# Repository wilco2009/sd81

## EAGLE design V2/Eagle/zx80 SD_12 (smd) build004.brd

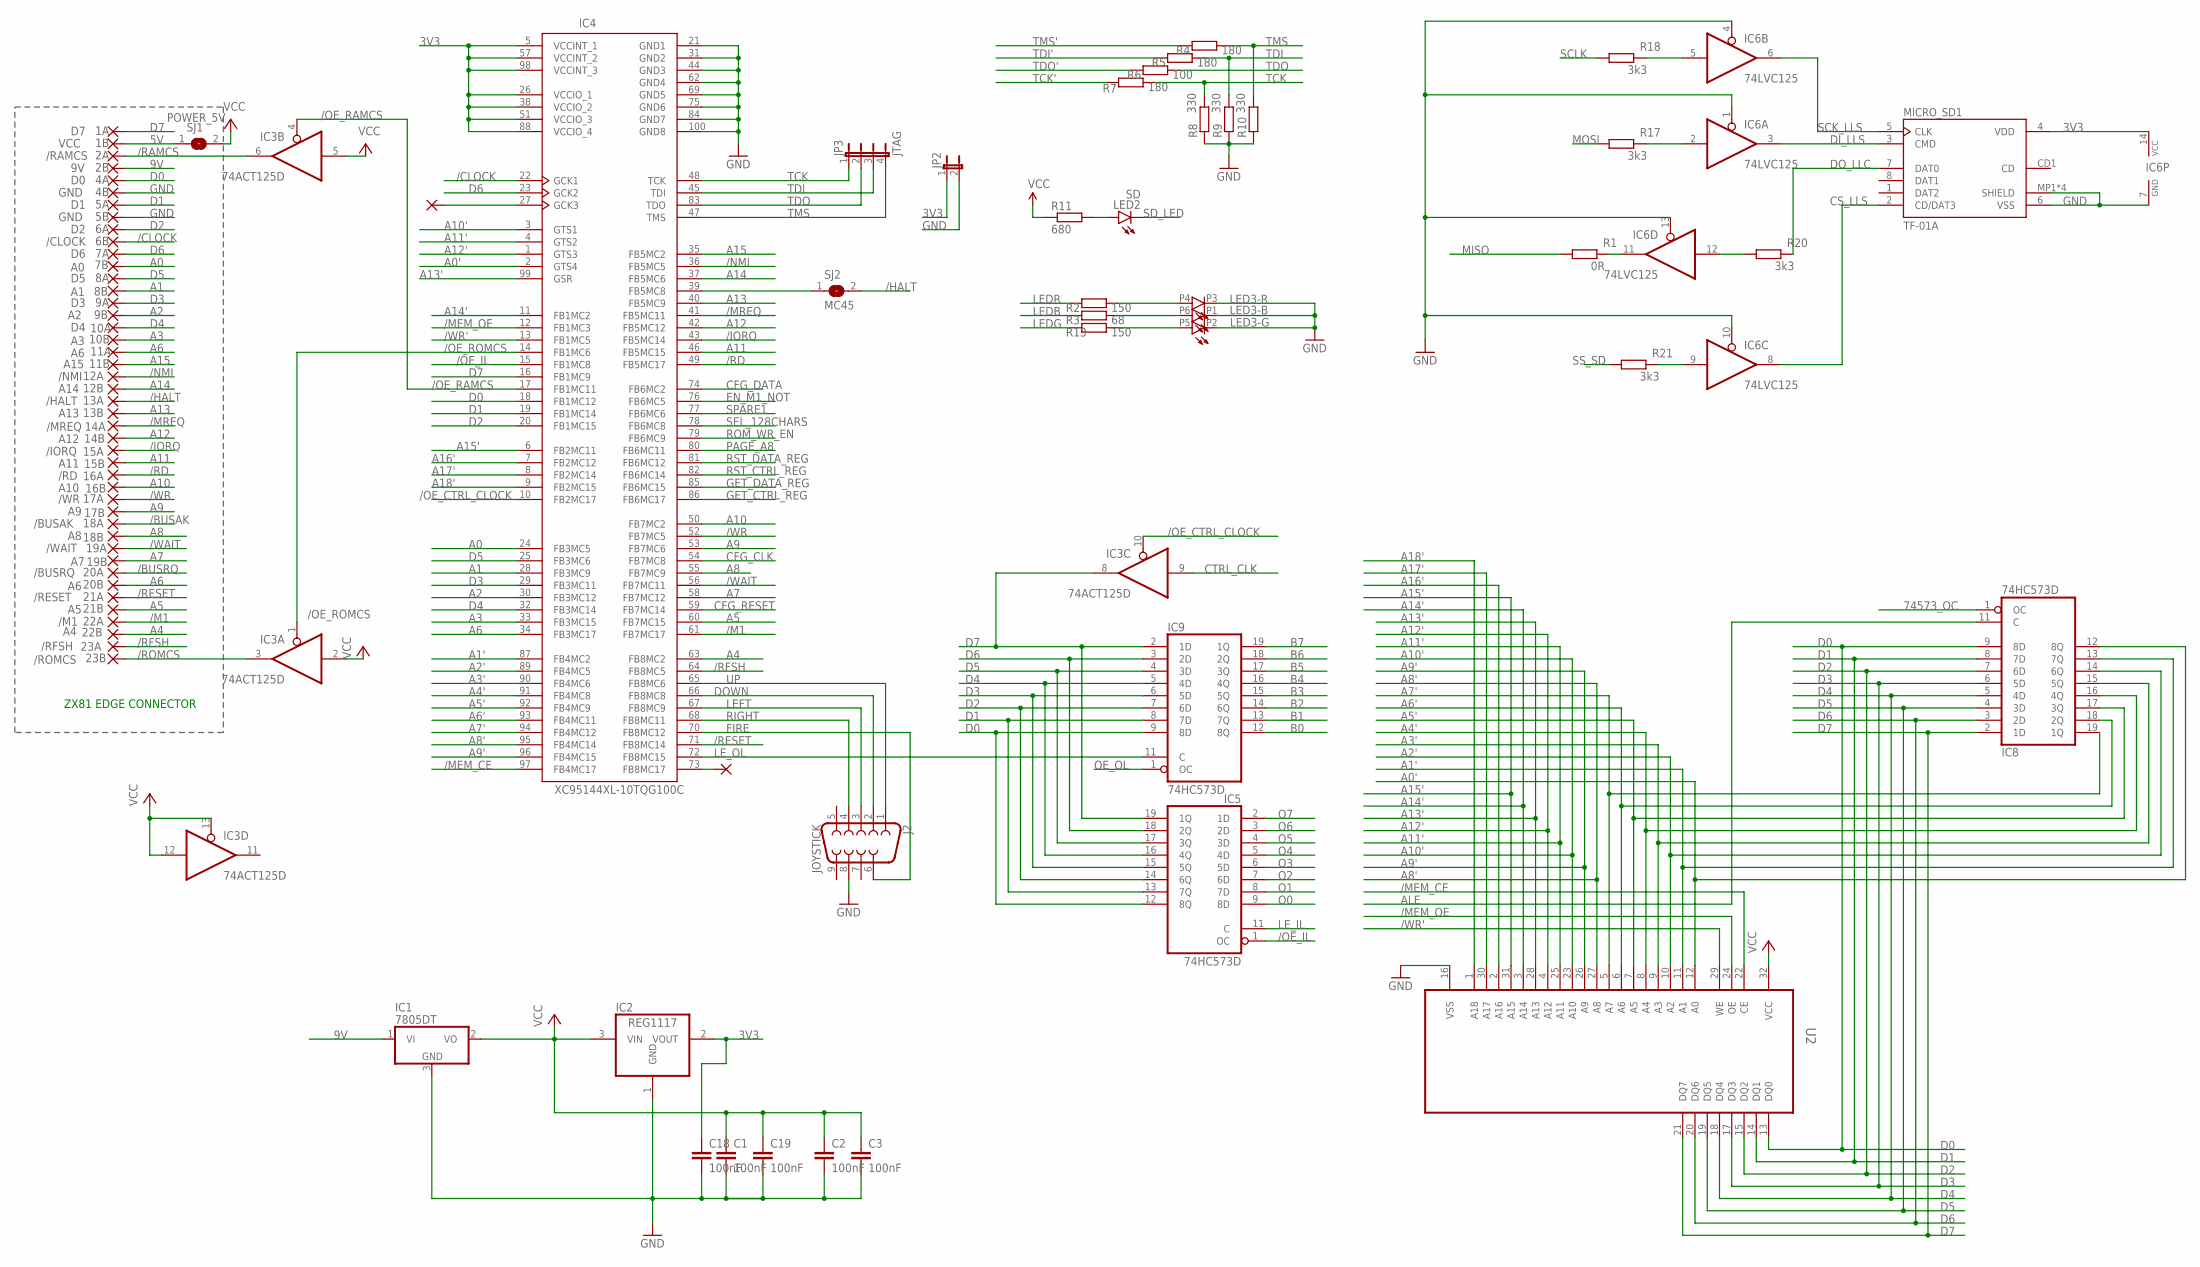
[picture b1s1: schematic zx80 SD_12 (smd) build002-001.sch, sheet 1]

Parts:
1A: D7; EDGEPIN
1B: VCC; EDGEPIN
2A: /RAMCS; EDGEPIN
2B: 9V; EDGEPIN
4A: D0; EDGEPIN
4B, 5B: GND; EDGEPIN
5A: D1; EDGEPIN
6A: D2; EDGEPIN
6B: /CLOCK; EDGEPIN
7A: D6; EDGEPIN
7B: A0; EDGEPIN
8A: D5; EDGEPIN
8B: A1; EDGEPIN
9A: D3; EDGEPIN
9B: A2; EDGEPIN
10A: D4; EDGEPIN
10B: A3; EDGEPIN
11A, 20B: A6; EDGEPIN
11B: A15; EDGEPIN
12A: /NMI; EDGEPIN
12B: A14; EDGEPIN
13A: /HALT; EDGEPIN
13B: A13; EDGEPIN
14A: /MREQ; EDGEPIN
14B: A12; EDGEPIN
15A: /IORQ; EDGEPIN
15B: A11; EDGEPIN
16A: /RD; EDGEPIN
16B: A10; EDGEPIN
17A: /WR; EDGEPIN
17B: A9; EDGEPIN
18A: /BUSAK; EDGEPIN
18B: A8; EDGEPIN
19A: /WAIT; EDGEPIN
19B: A7; EDGEPIN
20A: /BUSRQ; EDGEPIN
21A: /RESET; EDGEPIN
21B: A5; EDGEPIN
22A: /M1; EDGEPIN
22B: A4; EDGEPIN
23A: /RFSH; EDGEPIN
23B: /ROMCS; EDGEPIN
C1, C2, C3, C18, C19: 100nF; C0603
IC1: 7805DT; TO252
IC2: REG1117; SOT223
IC3: 74ACT125D; SO14
IC4: XC95144XL-10TQG100C; TQFP100
IC5, IC8, IC9: 74HC573D; SO20W
IC6: 74LVC125; SO14
J2: JOYSTICK; DB9_MALE
JP2: JP1E; JP1
JP3: JTAG; JP4
LED2: SD; CHIPLED_0603
LED3: RS-3535MWAR; 3535-PLCC6
MICRO_SD1: TF-01A
PAD1: 1,6/0,8
PAD6: P73; 1,6/0,8
R1: 0R; R0603
R2, R13: 150; R0603
R3: 68; R0603
R4, R5, R7: 180; R0603
R6: 100; R0603
R8, R9, R10: 330; R0603
R11: 680; R0603
R17, R18, R20, R21: 3k3; R0603
SJ1: POWER_5V; SJ
SJ2: MC45; SJ
U2: AS6C4008-55SINSOP5; SOP32-5

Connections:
3V3: C18.1, IC2.2 (VOUT), IC4.5 (VCCINT_1), IC4.26 (VCCIO_1), IC4.38 (VCCIO_2), IC4.51 (VCCIO_3), IC4.57 (VCCINT_2), IC4.88 (VCCIO_4), IC4.98 (VCCINT_3), IC6.14 (VCC), JP2.1, MICRO_SD1.4 (VDD); also elsewhere on the board
5V: 1B.1, SJ1.1
9V: 2B.1, IC1.1 (VI)
/BUSAK: 18A.1
/BUSRQ: 20A.1
/CLOCK: 6B.1, IC4.22 (GCK1); also elsewhere on the board
/HALT: 13A.1, SJ2.2
/IORQ: 15A.1, IC4.43 (FB5MC14); also elsewhere on the board
/M1: 22A.1, IC4.61 (FB7MC17); also elsewhere on the board
/MEM_CE: IC4.97 (FB4MC17), U2.22 (CE); also elsewhere on the board
/MEM_OE: IC4.12 (FB1MC3), U2.24 (OE); also elsewhere on the board
/MREQ: 14A.1, IC4.41 (FB5MC11); also elsewhere on the board
/NMI: 12A.1, IC4.36 (FB5MC5); also elsewhere on the board
/OE_CTRL_CLOCK: IC3.10 (OE), IC4.10 (FB2MC17)
/OE_RAMCS: IC3.4 (OE), IC4.17 (FB1MC11)
/OE_ROMCS: IC3.1 (OE), IC4.14 (FB1MC6)
/RAMCS: 2A.1, IC3.6 (O); also elsewhere on the board
/RD: 16A.1, IC4.49 (FB5MC17); also elsewhere on the board
/RESET: 21A.1, IC4.71 (FB8MC14); also elsewhere on the board
/RFSH: 23A.1, IC4.64 (FB8MC5); also elsewhere on the board
/ROMCS: 23B.1, IC3.3 (O); also elsewhere on the board
/WAIT: 19A.1, IC4.56 (FB7MC11); also elsewhere on the board
/WR: 17A.1, IC4.52 (FB7MC5); also elsewhere on the board
/WR': IC4.13 (FB1MC5), U2.29 (WE); also elsewhere on the board
A0: 7B.1, IC4.24 (FB3MC5); also elsewhere on the board
A0': IC4.2 (GTS4), IC8.12 (8Q), U2.12 (A0); also elsewhere on the board
A1: 8B.1, IC4.28 (FB3MC9); also elsewhere on the board
A1': IC4.87 (FB4MC2), IC8.13 (7Q), U2.11 (A1); also elsewhere on the board
A2: 9B.1, IC4.30 (FB3MC12); also elsewhere on the board
A2': IC4.89 (FB4MC5), IC8.14 (6Q), U2.10 (A2); also elsewhere on the board
A3: 10B.1, IC4.33 (FB3MC15); also elsewhere on the board
A3': IC4.90 (FB4MC6), IC8.15 (5Q), U2.9 (A3); also elsewhere on the board
A4: 22B.1, IC4.63 (FB8MC2); also elsewhere on the board
A4': IC4.91 (FB4MC8), IC8.16 (4Q), U2.8 (A4); also elsewhere on the board
A5: 21B.1, IC4.60 (FB7MC15); also elsewhere on the board
A5': IC4.92 (FB4MC9), IC8.17 (3Q), U2.7 (A5); also elsewhere on the board
A6: 11A.1, 20B.1, IC4.34 (FB3MC17); also elsewhere on the board
A6': IC4.93 (FB4MC11), IC8.18 (2Q), U2.6 (A6); also elsewhere on the board
A7: 19B.1, IC4.58 (FB7MC12); also elsewhere on the board
A7': IC4.94 (FB4MC12), IC8.19 (1Q), U2.5 (A7); also elsewhere on the board
A8: 18B.1, IC4.55 (FB7MC9); also elsewhere on the board
A8': IC4.95 (FB4MC14), U2.27 (A8); also elsewhere on the board
A9: 17B.1, IC4.53 (FB7MC6); also elsewhere on the board
A9': IC4.96 (FB4MC15), U2.26 (A9); also elsewhere on the board
A10: 16B.1, IC4.50 (FB7MC2); also elsewhere on the board
A10': IC4.3 (GTS1), U2.23 (A10); also elsewhere on the board
A11: 15B.1, IC4.46 (FB5MC15); also elsewhere on the board
A11': IC4.4 (GTS2), U2.25 (A11); also elsewhere on the board
A12: 14B.1, IC4.42 (FB5MC12); also elsewhere on the board
A12': IC4.1 (GTS3), U2.4 (A12); also elsewhere on the board
A13: 13B.1, IC4.40 (FB5MC9); also elsewhere on the board
A13': IC4.99 (GSR), U2.28 (A13); also elsewhere on the board
A14: 12B.1, IC4.37 (FB5MC6); also elsewhere on the board
A14': IC4.11 (FB1MC2), U2.3 (A14); also elsewhere on the board
A15: 11B.1, IC4.35 (FB5MC2); also elsewhere on the board
A15': IC4.6 (FB2MC11), U2.31 (A15); also elsewhere on the board
A16': IC4.7 (FB2MC12), U2.2 (A16); also elsewhere on the board
A17': IC4.8 (FB2MC14), U2.30 (A17); also elsewhere on the board
A18': IC4.9 (FB2MC15), U2.1 (A18); also elsewhere on the board
ALE: IC8.11 (C); also elsewhere on the board
B0: IC9.12 (8Q); also elsewhere on the board
B1: IC9.13 (7Q); also elsewhere on the board
B2: IC9.14 (6Q); also elsewhere on the board
B3: IC9.15 (5Q); also elsewhere on the board
B4: IC9.16 (4Q); also elsewhere on the board
B5: IC9.17 (3Q); also elsewhere on the board
B6: IC9.18 (2Q); also elsewhere on the board
B7: IC9.19 (1Q); also elsewhere on the board
CFG_CLK: IC4.54 (FB7MC8); also elsewhere on the board
CFG_DATA: IC4.74 (FB6MC2); also elsewhere on the board
CFG_RESET: IC4.59 (FB7MC14); also elsewhere on the board
CS_LLS: IC6.8 (O), MICRO_SD1.2 (CD/DAT3)
CTRL_CLK: IC3.9 (I); also elsewhere on the board
D0: 4A.1, IC4.18 (FB1MC12), IC5.12 (8Q), IC8.9 (8D), IC9.9 (8D), U2.13 (DQ0); also elsewhere on the board
D1: 5A.1, IC4.19 (FB1MC14), IC5.13 (7Q), IC8.8 (7D), IC9.8 (7D), U2.14 (DQ1); also elsewhere on the board
D2: 6A.1, IC4.20 (FB1MC15), IC5.14 (6Q), IC8.7 (6D), IC9.7 (6D), U2.15 (DQ2); also elsewhere on the board
D3: 9A.1, IC4.29 (FB3MC11), IC5.15 (5Q), IC8.6 (5D), IC9.6 (5D), U2.17 (DQ3); also elsewhere on the board
D4: 10A.1, IC4.32 (FB3MC14), IC5.16 (4Q), IC8.5 (4D), IC9.5 (4D), U2.18 (DQ4); also elsewhere on the board
D5: 8A.1, IC4.25 (FB3MC6), IC5.17 (3Q), IC8.4 (3D), IC9.4 (3D), U2.19 (DQ5); also elsewhere on the board
D6: 7A.1, IC4.23 (GCK2), IC5.18 (2Q), IC8.3 (2D), IC9.3 (2D), U2.20 (DQ6); also elsewhere on the board
D7: 1A.1, IC3.8 (O), IC4.16 (FB1MC9), IC5.19 (1Q), IC8.2 (1D), IC9.2 (1D), U2.21 (DQ7); also elsewhere on the board
DI_LLS: IC6.3 (O), MICRO_SD1.3 (CMD)
DOWN: IC4.66 (FB8MC8), J2.2; also elsewhere on the board
DO_LLC: IC6.12 (I), R20.1
EN_M1_NOT: IC4.76 (FB6MC5); also elsewhere on the board
FIRE: IC4.70 (FB8MC12), J2.6; also elsewhere on the board
GET_CTRL_REG: IC4.86 (FB6MC17); also elsewhere on the board
GET_DATA_REG: IC4.85 (FB6MC15); also elsewhere on the board
LEDB: R3.1; also elsewhere on the board
LEDG: R13.1; also elsewhere on the board
LEDR: R2.1; also elsewhere on the board
LEFT: IC4.67 (FB8MC9), J2.3; also elsewhere on the board
LE_IL: IC5.11 (C); also elsewhere on the board
LE_OL: IC4.72 (FB8MC15), IC9.11 (C)
MISO: R1.1; also elsewhere on the board
MOSI: R17.1; also elsewhere on the board
unnamed: IC6.2 (I), R17.2
unnamed: IC6.11 (O), R1.2
unnamed: IC6.5 (I), R18.2
unnamed: MICRO_SD1.7 (DAT0), R20.2
unnamed: IC6.9 (I), R21.2
unnamed: LED2.A, R11.2
unnamed: IC4.73 (FB8MC17), PAD6.1
unnamed: IC4.27 (GCK3), PAD1.1
unnamed: LED3.P4 (A), R2.2
unnamed: LED3.P6 (A), R3.2
unnamed: LED3.P5 (A), R13.2
O0: IC5.9 (8D); also elsewhere on the board
O1: IC5.8 (7D); also elsewhere on the board
O2: IC5.7 (6D); also elsewhere on the board
O3: IC5.6 (5D); also elsewhere on the board
O4: IC5.5 (4D); also elsewhere on the board
O5: IC5.4 (3D); also elsewhere on the board
PAGE_A8: IC4.80 (FB6MC11); also elsewhere on the board
RIGHT: IC4.68 (FB8MC11), J2.4; also elsewhere on the board
ROM_WR_EN: IC4.79 (FB6MC9); also elsewhere on the board
RST_CTRL_REG: IC4.82 (FB6MC14); also elsewhere on the board
RST_DATA_REG: IC4.81 (FB6MC12); also elsewhere on the board
SCK_LLS: IC6.6 (O), MICRO_SD1.5 (CLK)
SCLK: R18.1; also elsewhere on the board
SD_LED: LED2.C; also elsewhere on the board
SEL_128CHARS: IC4.78 (FB6MC8); also elsewhere on the board
SPARE1: IC4.77 (FB6MC6); also elsewhere on the board
SS_SD: R21.1; also elsewhere on the board
TCK: IC4.48 (TCK), JP3.1, R7.2, R8.2; also elsewhere on the board
TCK': R7.1; also elsewhere on the board
TDI: IC4.45 (TDI), JP3.3, R5.2, R9.2; also elsewhere on the board
TDI': R5.1; also elsewhere on the board
TDO: IC4.83 (TDO), JP3.2, R6.2; also elsewhere on the board
TDO': R6.1; also elsewhere on the board
TMS: IC4.47 (TMS), JP3.4, R4.2, R10.2; also elsewhere on the board
TMS': R4.1; also elsewhere on the board
UP: IC4.65 (FB8MC6), J2.1; also elsewhere on the board

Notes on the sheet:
ZX81 EDGE CONNECTOR

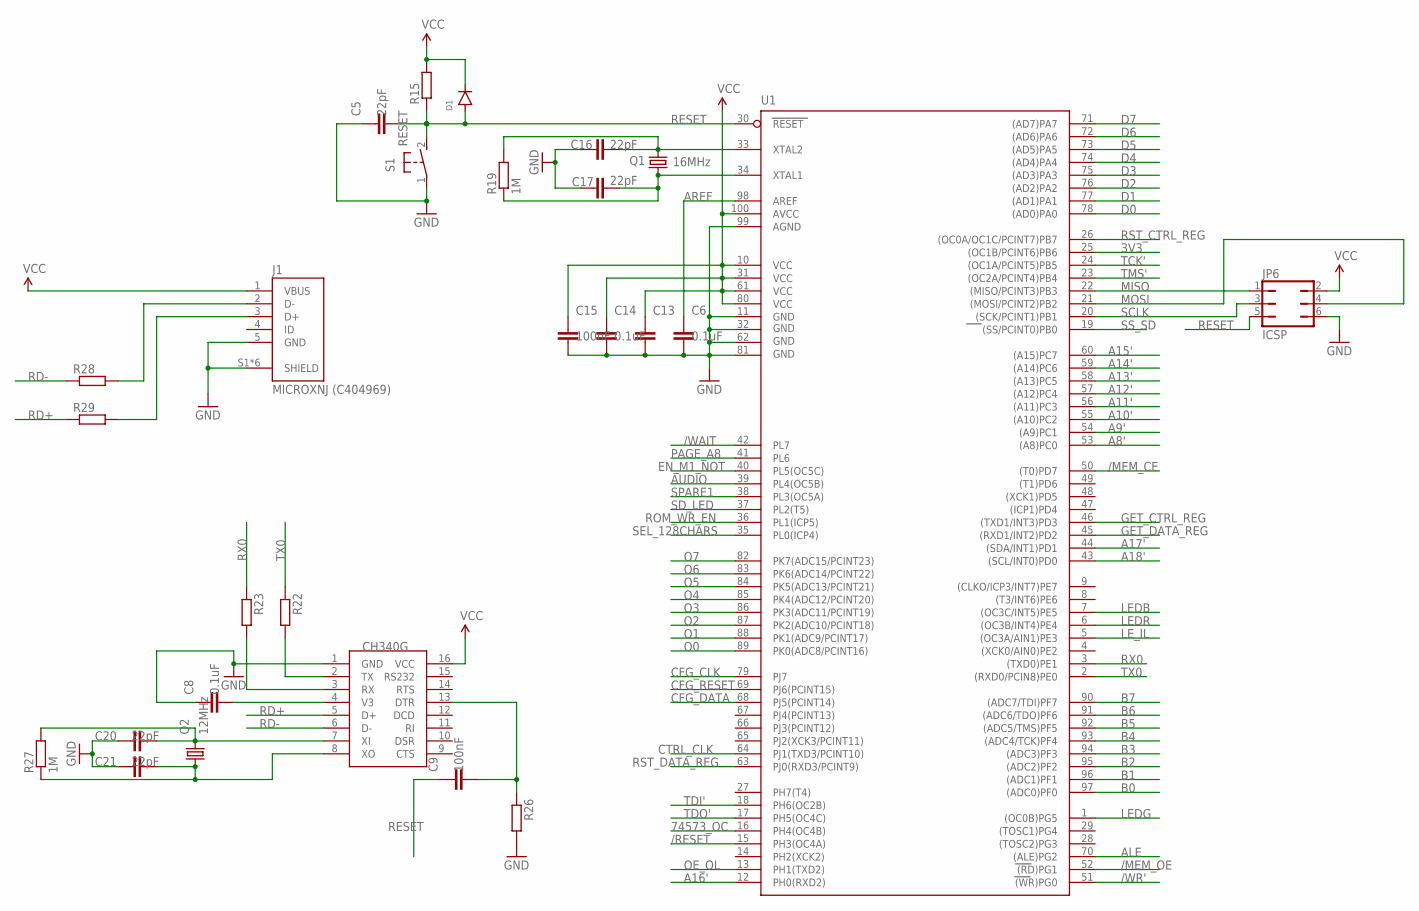
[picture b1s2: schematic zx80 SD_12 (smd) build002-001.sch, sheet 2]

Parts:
C5, C16, C17, C20, C21: 22pF; C0603
C6, C8, C13, C14: 0.1uF; C0603
C9, C15: 100nF; C0603
D1: DIODE-SOD123; SOD123
IC7: CH340G; SOIC16
J1: MICROXNJ (C404969); SHOUHAN_MICROXNJ
JP6: ICSP; JP3Q
Q1: 16MHz; 3.2X2.5_KX-7
Q2: 12MHz; 3.2X2.5_KX-7
R15: R0603
R19, R27: 1M; R0603
R22, R23, R26: 1K; R0603
R28, R29: 22R; R0603
S1: RESET; B3F-31XX
U1: ATMEGA2560AU; TQFP100

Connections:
3V3: U1.25 ((OC1B/PCINT6)PB6); also elsewhere on the board
/MEM_CE: U1.50 ((T0)PD7); also elsewhere on the board
/MEM_OE: U1.52 ((RD)PG1); also elsewhere on the board
/RESET: U1.15 (PH3(OC4A)); also elsewhere on the board
/WAIT: U1.42 (PL7); also elsewhere on the board
/WR': U1.51 ((WR)PG0); also elsewhere on the board
A8': U1.53 ((A8)PC0); also elsewhere on the board
A9': U1.54 ((A9)PC1); also elsewhere on the board
A10': U1.55 ((A10)PC2); also elsewhere on the board
A11': U1.56 ((A11)PC3); also elsewhere on the board
A12': U1.57 ((A12)PC4); also elsewhere on the board
A13': U1.58 ((A13)PC5); also elsewhere on the board
A14': U1.59 ((A14)PC6); also elsewhere on the board
A15': U1.60 ((A15)PC7); also elsewhere on the board
A16': U1.12 (PH0(RXD2)); also elsewhere on the board
ALE: U1.70 ((ALE)PG2); also elsewhere on the board
AREF: C6.1, U1.98 (AREF)
AUDIO: U1.39 (PL4(OC5B))
B0: U1.97 ((ADC0)PF0); also elsewhere on the board
B1: U1.96 ((ADC1)PF1); also elsewhere on the board
B2: U1.95 ((ADC2)PF2); also elsewhere on the board
B3: U1.94 ((ADC3)PF3); also elsewhere on the board
B4: U1.93 ((ADC4/TCK)PF4); also elsewhere on the board
B5: U1.92 ((ADC5/TMS)PF5); also elsewhere on the board
B6: U1.91 ((ADC6/TDO)PF6); also elsewhere on the board
B7: U1.90 ((ADC7/TDI)PF7); also elsewhere on the board
CFG_CLK: U1.79 (PJ7); also elsewhere on the board
CFG_DATA: U1.68 (PJ5(PCINT14)); also elsewhere on the board
CFG_RESET: U1.69 (PJ6(PCINT15)); also elsewhere on the board
CTRL_CLK: U1.64 (PJ1(TXD3/PCINT10)); also elsewhere on the board
D0: U1.78 ((AD0)PA0); also elsewhere on the board
D1: U1.77 ((AD1)PA1); also elsewhere on the board
D2: U1.76 ((AD2)PA2); also elsewhere on the board
D3: U1.75 ((AD3)PA3); also elsewhere on the board
D4: U1.74 ((AD4)PA4); also elsewhere on the board
D5: U1.73 ((AD5)PA5); also elsewhere on the board
D6: U1.72 ((AD6)PA6); also elsewhere on the board
D7: U1.71 ((AD7)PA7); also elsewhere on the board
EN_M1_NOT: U1.40 (PL5(OC5C)); also elsewhere on the board
GET_CTRL_REG: U1.46 ((TXD1/INT3)PD3); also elsewhere on the board
GET_DATA_REG: U1.45 ((RXD1/INT2)PD2); also elsewhere on the board
LEDB: U1.7 ((OC3C/INT5)PE5); also elsewhere on the board
LEDG: U1.1 ((OC0B)PG5); also elsewhere on the board
LEDR: U1.6 ((OC3B/INT4)PE4); also elsewhere on the board
LE_IL: U1.5 ((OC3A/AIN1)PE3); also elsewhere on the board
MISO: JP6.1, U1.22 ((MISO/PCINT3)PB3); also elsewhere on the board
MOSI: JP6.4, U1.21 ((MOSI/PCINT2)PB2); also elsewhere on the board
unnamed: IC7.2 (TX), R22.2
unnamed: IC7.3 (RX), R23.2
unnamed: C8.2, IC7.4 (V3)
unnamed: C20.2, IC7.7 (XI), Q2.3 (2), R27.2
unnamed: C21.2, IC7.8 (XO), Q2.1, R27.1
unnamed: C16.2, Q1.3 (2), R19.2, U1.33 (XTAL2)
unnamed: C17.2, Q1.1, R19.1, U1.34 (XTAL1)
unnamed: C9.2, IC7.13 (DTR), R26.1
unnamed: J1.2 (D-), R28.2
unnamed: J1.3 (D+), R29.2
O0: U1.89 (PK0(ADC8/PCINT16)); also elsewhere on the board
O1: U1.88 (PK1(ADC9/PCINT17)); also elsewhere on the board
O2: U1.87 (PK2(ADC10/PCINT18)); also elsewhere on the board
O3: U1.86 (PK3(ADC11/PCINT19)); also elsewhere on the board
O4: U1.85 (PK4(ADC12/PCINT20)); also elsewhere on the board
O5: U1.84 (PK5(ADC13/PCINT21)); also elsewhere on the board
PAGE_A8: U1.41 (PL6); also elsewhere on the board
RD+: IC7.5 (D+), R29.1
RD-: IC7.6 (D-), R28.1
RESET: C5.2, C9.1, D1.A, JP6.5, R15.1, S1.2 (S), U1.30 (RESET)
ROM_WR_EN: U1.36 (PL1(ICP5)); also elsewhere on the board
RST_CTRL_REG: U1.26 ((OC0A/OC1C/PCINT7)PB7); also elsewhere on the board
RST_DATA_REG: U1.63 (PJ0(RXD3/PCINT9)); also elsewhere on the board
RX0: R23.1, U1.3 ((TXD0)PE1)
SCLK: JP6.3, U1.20 ((SCK/PCINT1)PB1); also elsewhere on the board
SD_LED: U1.37 (PL2(T5)); also elsewhere on the board
SEL_128CHARS: U1.35 (PL0(ICP4)); also elsewhere on the board
SPARE1: U1.38 (PL3(OC5A)); also elsewhere on the board
SS_SD: U1.19 ((SS/PCINT0)PB0); also elsewhere on the board
TCK': U1.24 ((OC1A/PCINT5)PB5); also elsewhere on the board
TDI': U1.18 (PH6(OC2B)); also elsewhere on the board
TDO': U1.17 (PH5(OC4C)); also elsewhere on the board
TMS': U1.23 ((OC2A/PCINT4)PB4); also elsewhere on the board
TX0: R22.1, U1.2 ((RXD0/PCIN8)PE0)

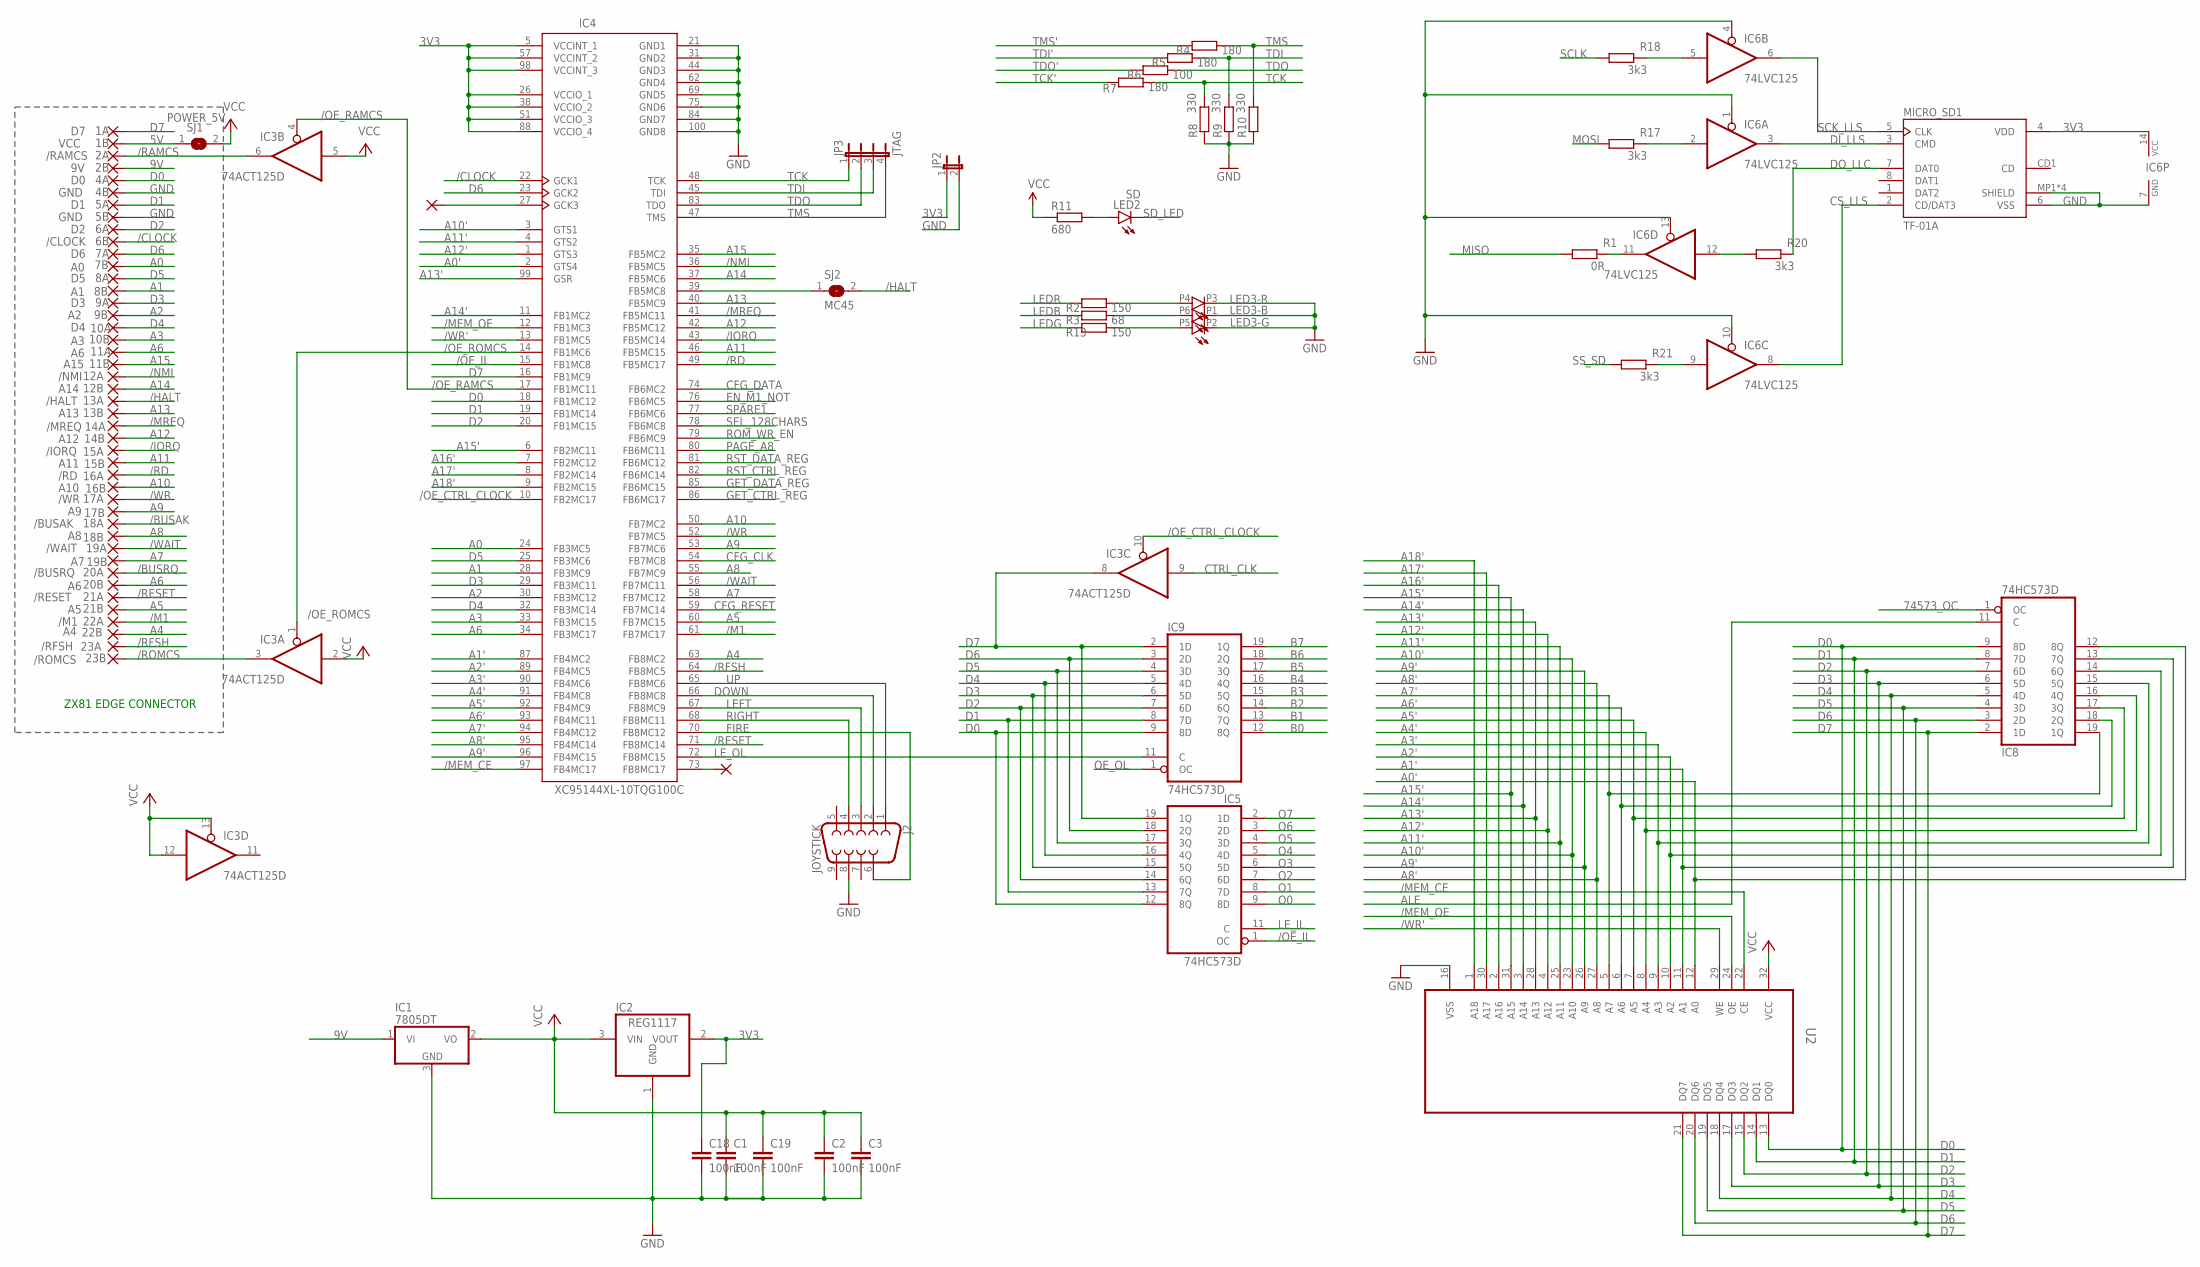
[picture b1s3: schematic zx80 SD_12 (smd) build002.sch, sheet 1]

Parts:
1A: D7; EDGEPIN
1B: VCC; EDGEPIN
2A: /RAMCS; EDGEPIN
2B: 9V; EDGEPIN
4A: D0; EDGEPIN
4B, 5B: GND; EDGEPIN
5A: D1; EDGEPIN
6A: D2; EDGEPIN
6B: /CLOCK; EDGEPIN
7A: D6; EDGEPIN
7B: A0; EDGEPIN
8A: D5; EDGEPIN
8B: A1; EDGEPIN
9A: D3; EDGEPIN
9B: A2; EDGEPIN
10A: D4; EDGEPIN
10B: A3; EDGEPIN
11A, 20B: A6; EDGEPIN
11B: A15; EDGEPIN
12A: /NMI; EDGEPIN
12B: A14; EDGEPIN
13A: /HALT; EDGEPIN
13B: A13; EDGEPIN
14A: /MREQ; EDGEPIN
14B: A12; EDGEPIN
15A: /IORQ; EDGEPIN
15B: A11; EDGEPIN
16A: /RD; EDGEPIN
16B: A10; EDGEPIN
17A: /WR; EDGEPIN
17B: A9; EDGEPIN
18A: /BUSAK; EDGEPIN
18B: A8; EDGEPIN
19A: /WAIT; EDGEPIN
19B: A7; EDGEPIN
20A: /BUSRQ; EDGEPIN
21A: /RESET; EDGEPIN
21B: A5; EDGEPIN
22A: /M1; EDGEPIN
22B: A4; EDGEPIN
23A: /RFSH; EDGEPIN
23B: /ROMCS; EDGEPIN
C1, C2, C3, C18, C19: 100nF; C0603
IC1: 7805DT; TO252
IC2: REG1117; SOT223
IC3: 74ACT125D; SO14
IC4: XC95144XL-10TQG100C; TQFP100
IC5, IC8, IC9: 74HC573D; SO20W
IC6: 74LVC125; SO14
J2: JOYSTICK; DB9_MALE
JP2: JP1E; JP1
JP3: JTAG; JP4
LED2: SD; CHIPLED_0603
LED3: STATUS; 3535-PLCC6
MICRO_SD1: TF-01A
PAD1: 1,6/0,8
PAD6: P73; 1,6/0,8
R1: 0R; R0603
R2, R13: 150; R0603
R3: 68; R0603
R4, R5, R7: 180; R0603
R6: 100; R0603
R8, R9, R10: 330; R0603
R11: 680; R0603
R17, R18, R20, R21: 3k3; R0603
SJ1: POWER_5V; SJ
SJ2: MC45; SJ
U2: AS6C4008-55SINSOP5; SOP32-5

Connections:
3V3: C18.1, IC2.2 (VOUT), IC4.5 (VCCINT_1), IC4.26 (VCCIO_1), IC4.38 (VCCIO_2), IC4.51 (VCCIO_3), IC4.57 (VCCINT_2), IC4.88 (VCCIO_4), IC4.98 (VCCINT_3), IC6.14 (VCC), JP2.1, MICRO_SD1.4 (VDD); also elsewhere on the board
5V: 1B.1, SJ1.1
9V: 2B.1, IC1.1 (VI)
/BUSAK: 18A.1
/BUSRQ: 20A.1
/CLOCK: 6B.1, IC4.22 (GCK1); also elsewhere on the board
/HALT: 13A.1, SJ2.2
/IORQ: 15A.1, IC4.43 (FB5MC14); also elsewhere on the board
/M1: 22A.1, IC4.61 (FB7MC17); also elsewhere on the board
/MEM_CE: IC4.97 (FB4MC17), U2.22 (CE); also elsewhere on the board
/MEM_OE: IC4.12 (FB1MC3), U2.24 (OE); also elsewhere on the board
/MREQ: 14A.1, IC4.41 (FB5MC11); also elsewhere on the board
/NMI: 12A.1, IC4.36 (FB5MC5); also elsewhere on the board
/OE_CTRL_CLOCK: IC3.10 (OE), IC4.10 (FB2MC17)
/OE_RAMCS: IC3.4 (OE), IC4.17 (FB1MC11)
/OE_ROMCS: IC3.1 (OE), IC4.14 (FB1MC6)
/RAMCS: 2A.1, IC3.6 (O); also elsewhere on the board
/RD: 16A.1, IC4.49 (FB5MC17); also elsewhere on the board
/RESET: 21A.1, IC4.71 (FB8MC14); also elsewhere on the board
/RFSH: 23A.1, IC4.64 (FB8MC5); also elsewhere on the board
/ROMCS: 23B.1, IC3.3 (O); also elsewhere on the board
/WAIT: 19A.1, IC4.56 (FB7MC11); also elsewhere on the board
/WR: 17A.1, IC4.52 (FB7MC5); also elsewhere on the board
/WR': IC4.13 (FB1MC5), U2.29 (WE); also elsewhere on the board
A0: 7B.1, IC4.24 (FB3MC5); also elsewhere on the board
A0': IC4.2 (GTS4), IC8.12 (8Q), U2.12 (A0); also elsewhere on the board
A1: 8B.1, IC4.28 (FB3MC9); also elsewhere on the board
A1': IC4.87 (FB4MC2), IC8.13 (7Q), U2.11 (A1); also elsewhere on the board
A2: 9B.1, IC4.30 (FB3MC12); also elsewhere on the board
A2': IC4.89 (FB4MC5), IC8.14 (6Q), U2.10 (A2); also elsewhere on the board
A3: 10B.1, IC4.33 (FB3MC15); also elsewhere on the board
A3': IC4.90 (FB4MC6), IC8.15 (5Q), U2.9 (A3); also elsewhere on the board
A4: 22B.1, IC4.63 (FB8MC2); also elsewhere on the board
A4': IC4.91 (FB4MC8), IC8.16 (4Q), U2.8 (A4); also elsewhere on the board
A5: 21B.1, IC4.60 (FB7MC15); also elsewhere on the board
A5': IC4.92 (FB4MC9), IC8.17 (3Q), U2.7 (A5); also elsewhere on the board
A6: 11A.1, 20B.1, IC4.34 (FB3MC17); also elsewhere on the board
A6': IC4.93 (FB4MC11), IC8.18 (2Q), U2.6 (A6); also elsewhere on the board
A7: 19B.1, IC4.58 (FB7MC12); also elsewhere on the board
A7': IC4.94 (FB4MC12), IC8.19 (1Q), U2.5 (A7); also elsewhere on the board
A8: 18B.1, IC4.55 (FB7MC9); also elsewhere on the board
A8': IC4.95 (FB4MC14), U2.27 (A8); also elsewhere on the board
A9: 17B.1, IC4.53 (FB7MC6); also elsewhere on the board
A9': IC4.96 (FB4MC15), U2.26 (A9); also elsewhere on the board
A10: 16B.1, IC4.50 (FB7MC2); also elsewhere on the board
A10': IC4.3 (GTS1), U2.23 (A10); also elsewhere on the board
A11: 15B.1, IC4.46 (FB5MC15); also elsewhere on the board
A11': IC4.4 (GTS2), U2.25 (A11); also elsewhere on the board
A12: 14B.1, IC4.42 (FB5MC12); also elsewhere on the board
A12': IC4.1 (GTS3), U2.4 (A12); also elsewhere on the board
A13: 13B.1, IC4.40 (FB5MC9); also elsewhere on the board
A13': IC4.99 (GSR), U2.28 (A13); also elsewhere on the board
A14: 12B.1, IC4.37 (FB5MC6); also elsewhere on the board
A14': IC4.11 (FB1MC2), U2.3 (A14); also elsewhere on the board
A15: 11B.1, IC4.35 (FB5MC2); also elsewhere on the board
A15': IC4.6 (FB2MC11), U2.31 (A15); also elsewhere on the board
A16': IC4.7 (FB2MC12), U2.2 (A16); also elsewhere on the board
A17': IC4.8 (FB2MC14), U2.30 (A17); also elsewhere on the board
A18': IC4.9 (FB2MC15), U2.1 (A18); also elsewhere on the board
ALE: IC8.11 (C); also elsewhere on the board
B0: IC9.12 (8Q); also elsewhere on the board
B1: IC9.13 (7Q); also elsewhere on the board
B2: IC9.14 (6Q); also elsewhere on the board
B3: IC9.15 (5Q); also elsewhere on the board
B4: IC9.16 (4Q); also elsewhere on the board
B5: IC9.17 (3Q); also elsewhere on the board
B6: IC9.18 (2Q); also elsewhere on the board
B7: IC9.19 (1Q); also elsewhere on the board
CFG_CLK: IC4.54 (FB7MC8); also elsewhere on the board
CFG_DATA: IC4.74 (FB6MC2); also elsewhere on the board
CFG_RESET: IC4.59 (FB7MC14); also elsewhere on the board
CS_LLS: IC6.8 (O), MICRO_SD1.2 (CD/DAT3)
CTRL_CLK: IC3.9 (I); also elsewhere on the board
D0: 4A.1, IC4.18 (FB1MC12), IC5.12 (8Q), IC8.9 (8D), IC9.9 (8D), U2.13 (DQ0); also elsewhere on the board
D1: 5A.1, IC4.19 (FB1MC14), IC5.13 (7Q), IC8.8 (7D), IC9.8 (7D), U2.14 (DQ1); also elsewhere on the board
D2: 6A.1, IC4.20 (FB1MC15), IC5.14 (6Q), IC8.7 (6D), IC9.7 (6D), U2.15 (DQ2); also elsewhere on the board
D3: 9A.1, IC4.29 (FB3MC11), IC5.15 (5Q), IC8.6 (5D), IC9.6 (5D), U2.17 (DQ3); also elsewhere on the board
D4: 10A.1, IC4.32 (FB3MC14), IC5.16 (4Q), IC8.5 (4D), IC9.5 (4D), U2.18 (DQ4); also elsewhere on the board
D5: 8A.1, IC4.25 (FB3MC6), IC5.17 (3Q), IC8.4 (3D), IC9.4 (3D), U2.19 (DQ5); also elsewhere on the board
D6: 7A.1, IC4.23 (GCK2), IC5.18 (2Q), IC8.3 (2D), IC9.3 (2D), U2.20 (DQ6); also elsewhere on the board
D7: 1A.1, IC3.8 (O), IC4.16 (FB1MC9), IC5.19 (1Q), IC8.2 (1D), IC9.2 (1D), U2.21 (DQ7); also elsewhere on the board
DI_LLS: IC6.3 (O), MICRO_SD1.3 (CMD)
DOWN: IC4.66 (FB8MC8), J2.2; also elsewhere on the board
DO_LLC: IC6.12 (I), R20.1
EN_M1_NOT: IC4.76 (FB6MC5); also elsewhere on the board
FIRE: IC4.70 (FB8MC12), J2.6; also elsewhere on the board
GET_CTRL_REG: IC4.86 (FB6MC17); also elsewhere on the board
GET_DATA_REG: IC4.85 (FB6MC15); also elsewhere on the board
LEDB: R3.1; also elsewhere on the board
LEDG: R13.1; also elsewhere on the board
LEDR: R2.1; also elsewhere on the board
LEFT: IC4.67 (FB8MC9), J2.3; also elsewhere on the board
LE_IL: IC5.11 (C); also elsewhere on the board
LE_OL: IC4.72 (FB8MC15), IC9.11 (C)
MISO: R1.1; also elsewhere on the board
MOSI: R17.1; also elsewhere on the board
unnamed: IC6.2 (I), R17.2
unnamed: IC6.11 (O), R1.2
unnamed: IC6.5 (I), R18.2
unnamed: MICRO_SD1.7 (DAT0), R20.2
unnamed: IC6.9 (I), R21.2
unnamed: LED2.A, R11.2
unnamed: IC4.73 (FB8MC17), PAD6.1
unnamed: IC4.27 (GCK3), PAD1.1
unnamed: LED3.P4 (A), R2.2
unnamed: LED3.P6 (A), R3.2
unnamed: LED3.P5 (A), R13.2
O0: IC5.9 (8D); also elsewhere on the board
O1: IC5.8 (7D); also elsewhere on the board
O2: IC5.7 (6D); also elsewhere on the board
O3: IC5.6 (5D); also elsewhere on the board
O4: IC5.5 (4D); also elsewhere on the board
O5: IC5.4 (3D); also elsewhere on the board
PAGE_A8: IC4.80 (FB6MC11); also elsewhere on the board
RIGHT: IC4.68 (FB8MC11), J2.4; also elsewhere on the board
ROM_WR_EN: IC4.79 (FB6MC9); also elsewhere on the board
RST_CTRL_REG: IC4.82 (FB6MC14); also elsewhere on the board
RST_DATA_REG: IC4.81 (FB6MC12); also elsewhere on the board
SCK_LLS: IC6.6 (O), MICRO_SD1.5 (CLK)
SCLK: R18.1; also elsewhere on the board
SD_LED: LED2.C; also elsewhere on the board
SEL_128CHARS: IC4.78 (FB6MC8); also elsewhere on the board
SPARE1: IC4.77 (FB6MC6); also elsewhere on the board
SS_SD: R21.1; also elsewhere on the board
TCK: IC4.48 (TCK), JP3.1, R7.2, R8.2; also elsewhere on the board
TCK': R7.1; also elsewhere on the board
TDI: IC4.45 (TDI), JP3.3, R5.2, R9.2; also elsewhere on the board
TDI': R5.1; also elsewhere on the board
TDO: IC4.83 (TDO), JP3.2, R6.2; also elsewhere on the board
TDO': R6.1; also elsewhere on the board
TMS: IC4.47 (TMS), JP3.4, R4.2, R10.2; also elsewhere on the board
TMS': R4.1; also elsewhere on the board
UP: IC4.65 (FB8MC6), J2.1; also elsewhere on the board

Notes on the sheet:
ZX81 EDGE CONNECTOR

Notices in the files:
V2/Eagle/zx80 SD_12 (smd) build004.brd:
COPYRIGHT 2025
V2/Eagle/zx81 SD_09.brd:
COPYRIGHT 2023
parts and their libraries:
SparkFun-Aesthetics: Licensing: Creative Commons ShareAlike 4.0 International - https://creativecommons.org/licenses/by-sa/4.0
crystal-geyer_V1_0: Copyright: Geyer-Electronic
